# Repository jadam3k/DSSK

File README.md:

# DSSK

## About The Project.
This project is just a USB -> UART -> USB converter using ESP32E. Thats simple project you get the same signals everywhere but this is cool and stupid :)

## SCREENS

## BOM

| References         | Value           | Footprint                     | Quantity |
|-------------------|-----------------|-------------------------------|---------:|
| C3, C4, C6, C7, C8 | 0.1uF          | C_0805_2012Metric             |        5 |
| C1, C2, C5         | 10uF           | C_0805_2012Metric             |        3 |
| R1, R2             | 10k            | R_0805_2012Metric             |        2 |
| U1, U3             | CH340C         | SOIC-16_3.9x9.9mm_P1.27mm     |        2 |
| U2                 | AMS1117-3.3    | SOT-223-3_TabPin2             |        1 |
| U4                 | ESP32-WROOM-32E| WIFI-SMD_ESP32-WROOM-32E      |        1 |
| SW1                | BOOT           | SW_PUSH_6mm                   |        1 |
| SW2                | RESET          | SW_PUSH_6mm                   |        1 |
| J1, J2             | USB_B_Micro    | USB_Micro-B_Molex-105017-0001 |        2 |

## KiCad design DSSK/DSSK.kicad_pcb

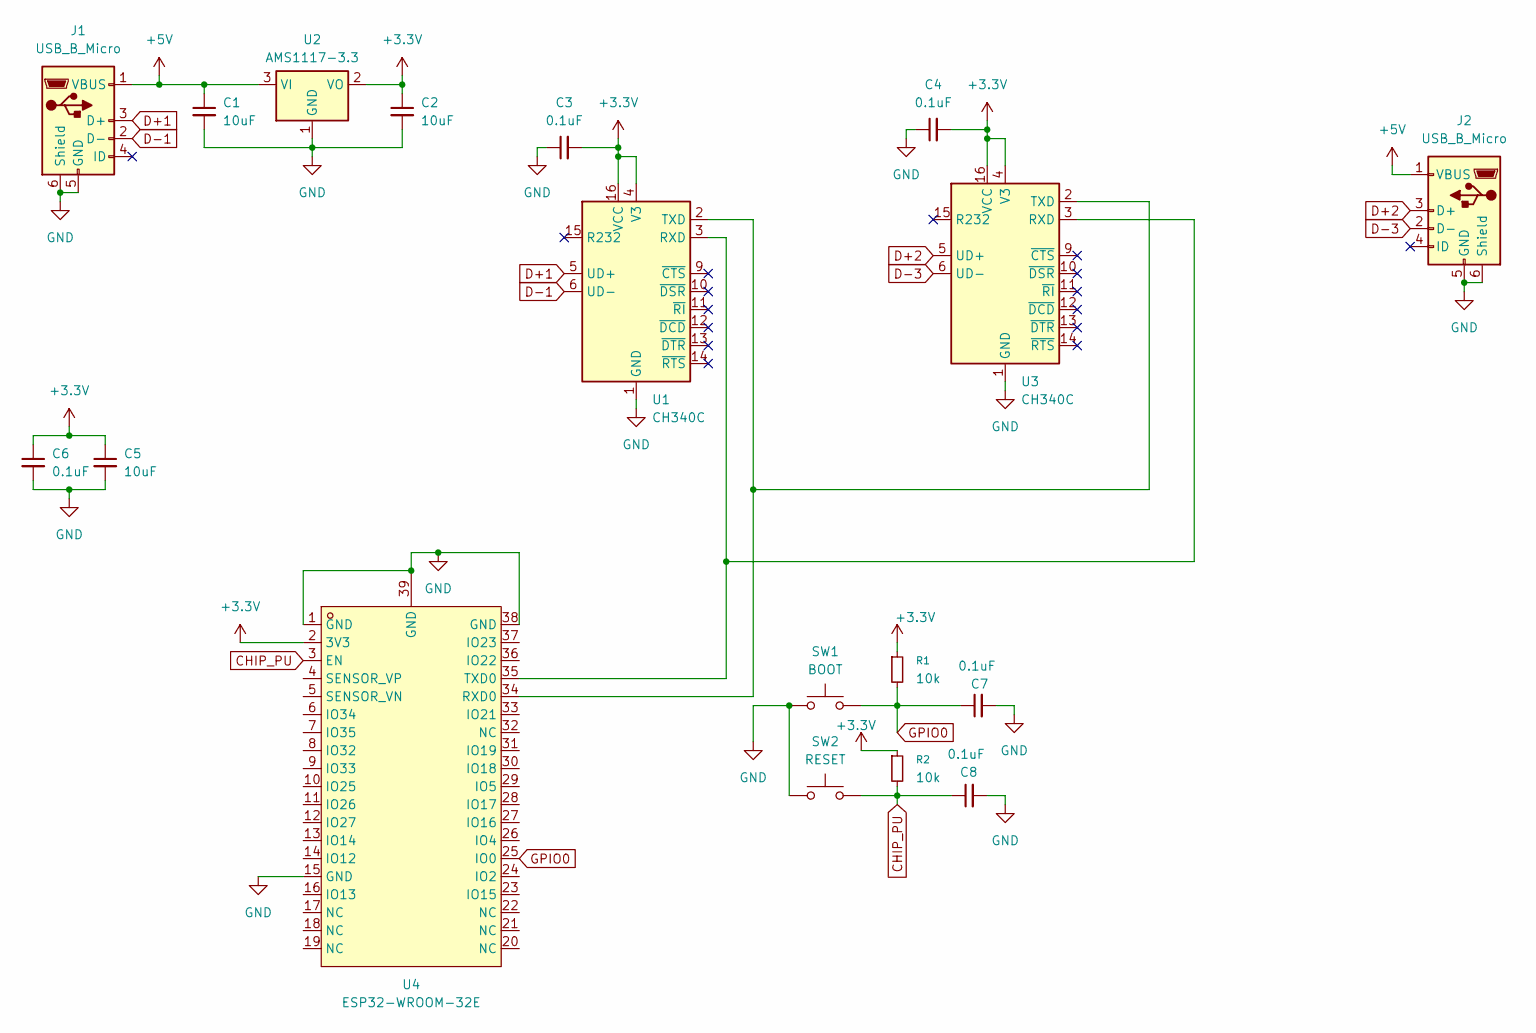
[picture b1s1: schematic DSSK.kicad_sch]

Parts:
C1, C2, C5: 10uF; C_0805_2012Metric
C3, C4, C6, C7, C8: 0.1uF; C_0805_2012Metric
J1, J2: USB_B_Micro; USB_Micro-B_Molex-105017-0001
R1, R2: 10k; R_0805_2012Metric
SW1: BOOT; SW_PUSH_6mm
SW2: RESET; SW_PUSH_6mm
U1, U3: CH340C; SOIC-16_3.9x9.9mm_P1.27mm
U2: AMS1117-3.3; SOT-223-3_TabPin2
U4: ESP32-WROOM-32E; WIFI-SMD_ESP32-WROOM-32E; MPN ESP32-WROOM-32E-N8; LCSC Part C701342

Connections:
+3.3V: C2.1, C3.2, C4.2, C5.1, C6.1, R1.1, R2.1, U1.4 (V3), U1.16 (VCC), U2.2 (VO), U3.4 (V3), U3.16 (VCC), U4.2 (3V3)
+5V: C1.1, J1.1 (VBUS), J2.1 (VBUS), U2.3 (VI)
CHIP_PU: C8.1, R2.2, SW2.2, U4.3 (EN)
D+1: J1.3 (D+), U1.5 (UD+)
D+2: J2.3 (D+), U3.5 (UD+)
D-1: J1.2 (D-), U1.6 (UD-)
D-3: J2.2 (D-), U3.6 (UD-)
GND: C1.2, C2.2, C3.1, C4.1, C5.2, C6.2, C7.2, C8.2, J1.5 (GND), J1.6 (Shield), J2.5 (GND), J2.6 (Shield), SW1.1, SW2.1, U1.1 (GND), U2.1 (GND), U3.1 (GND), U4.1 (GND), U4.15 (GND), U4.38 (GND), U4.39 (GND)
GPIO0: C7.1, R1.2, SW1.2, U4.25 (IO0)
unnamed: U1.3 (RXD), U3.3 (RXD), U4.35 (TXD0)
unnamed: U1.2 (TXD), U3.2 (TXD), U4.34 (RXD0)

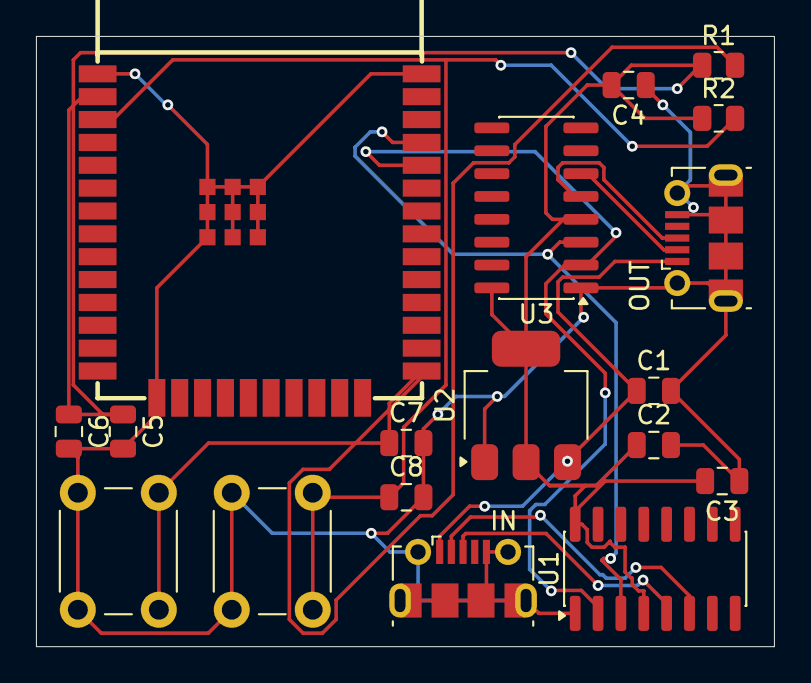
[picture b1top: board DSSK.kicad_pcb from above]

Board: 2 copper layers, 41.0 x 33.9 mm, 18 parts (0 on the bottom side), 11 nets.

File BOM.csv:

"","Sourced","Placed","References","Value","Footprint","Quantity"
1,"","","C3, C4, C6, C7, C8","0.1uF","C_0805_2012Metric",5
2,"","","C1, C2, C5","10uF","C_0805_2012Metric",3
3,"","","R1, R2","10k","R_0805_2012Metric",2
4,"","","U1, U3","CH340C","SOIC-16_3.9x9.9mm_P1.27mm",2
5,"","","U2","AMS1117-3.3","SOT-223-3_TabPin2",1
6,"","","U4","ESP32-WROOM-32E","WIFI-SMD_ESP32-WROOM-32E",1
7,"","","SW1","BOOT","SW_PUSH_6mm",1
8,"","","SW2","RESET","SW_PUSH_6mm",1
9,"","","J1, J2","USB_B_Micro","USB_Micro-B_Molex-105017-0001",2

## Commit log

2026-06-12 elo2
